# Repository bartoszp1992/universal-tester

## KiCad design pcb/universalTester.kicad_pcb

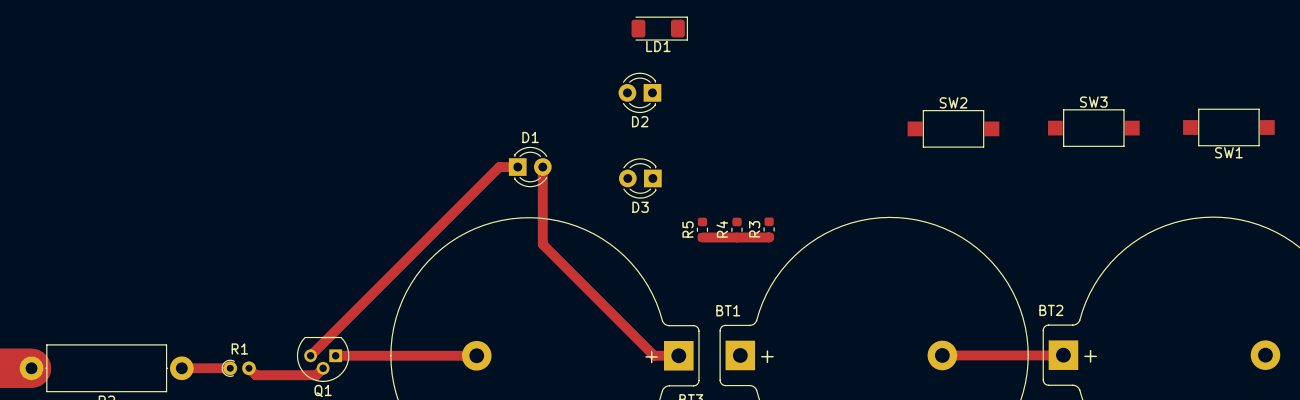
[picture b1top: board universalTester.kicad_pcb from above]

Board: 2 copper layers, 16 parts (0 on the bottom side), 12 nets.

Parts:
BT1, BT2, BT3: 2032; BatteryHolder_Keystone_106_1x20mm
D1: RED; LED_D3.0mm
D2: 410nm; LED_D3.0mm
D3: WH; LED_D3.0mm
LD1: RED; LED_1806_4516Metric
Q1: BC517; TO-92
R1: 4M7 1/4W; R_Axial_DIN0204_L3.6mm_D1.6mm_P1.90mm_Vertical
R2: 15M 2W; R_Axial_DIN0414_L11.9mm_D4.5mm_P15.24mm_Horizontal
R3, R4, R5: R; R_0603_1608Metric
SW1, SW2, SW3: SW_SPST; SW_SPST_CK_RS282G05A3

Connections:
GND: BT2.2, BT3.2, Q1.1, SW1.1, SW2.1, SW3.1
unnamed: BT1.1, R3.1, R4.1, R5.1
unnamed: BT1.2, BT2.1
unnamed: D1.1, Q1.3
unnamed: D2.1, SW2.2
unnamed: D2.2, R4.2
unnamed: D3.1, SW3.2
unnamed: D3.2, R5.2
unnamed: LD1.1, R3.2
unnamed: Q1.2, R1.2
unnamed: R1.1, R2.1
PLATE: BT3.1, D1.2

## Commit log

2020-09-27 initial
